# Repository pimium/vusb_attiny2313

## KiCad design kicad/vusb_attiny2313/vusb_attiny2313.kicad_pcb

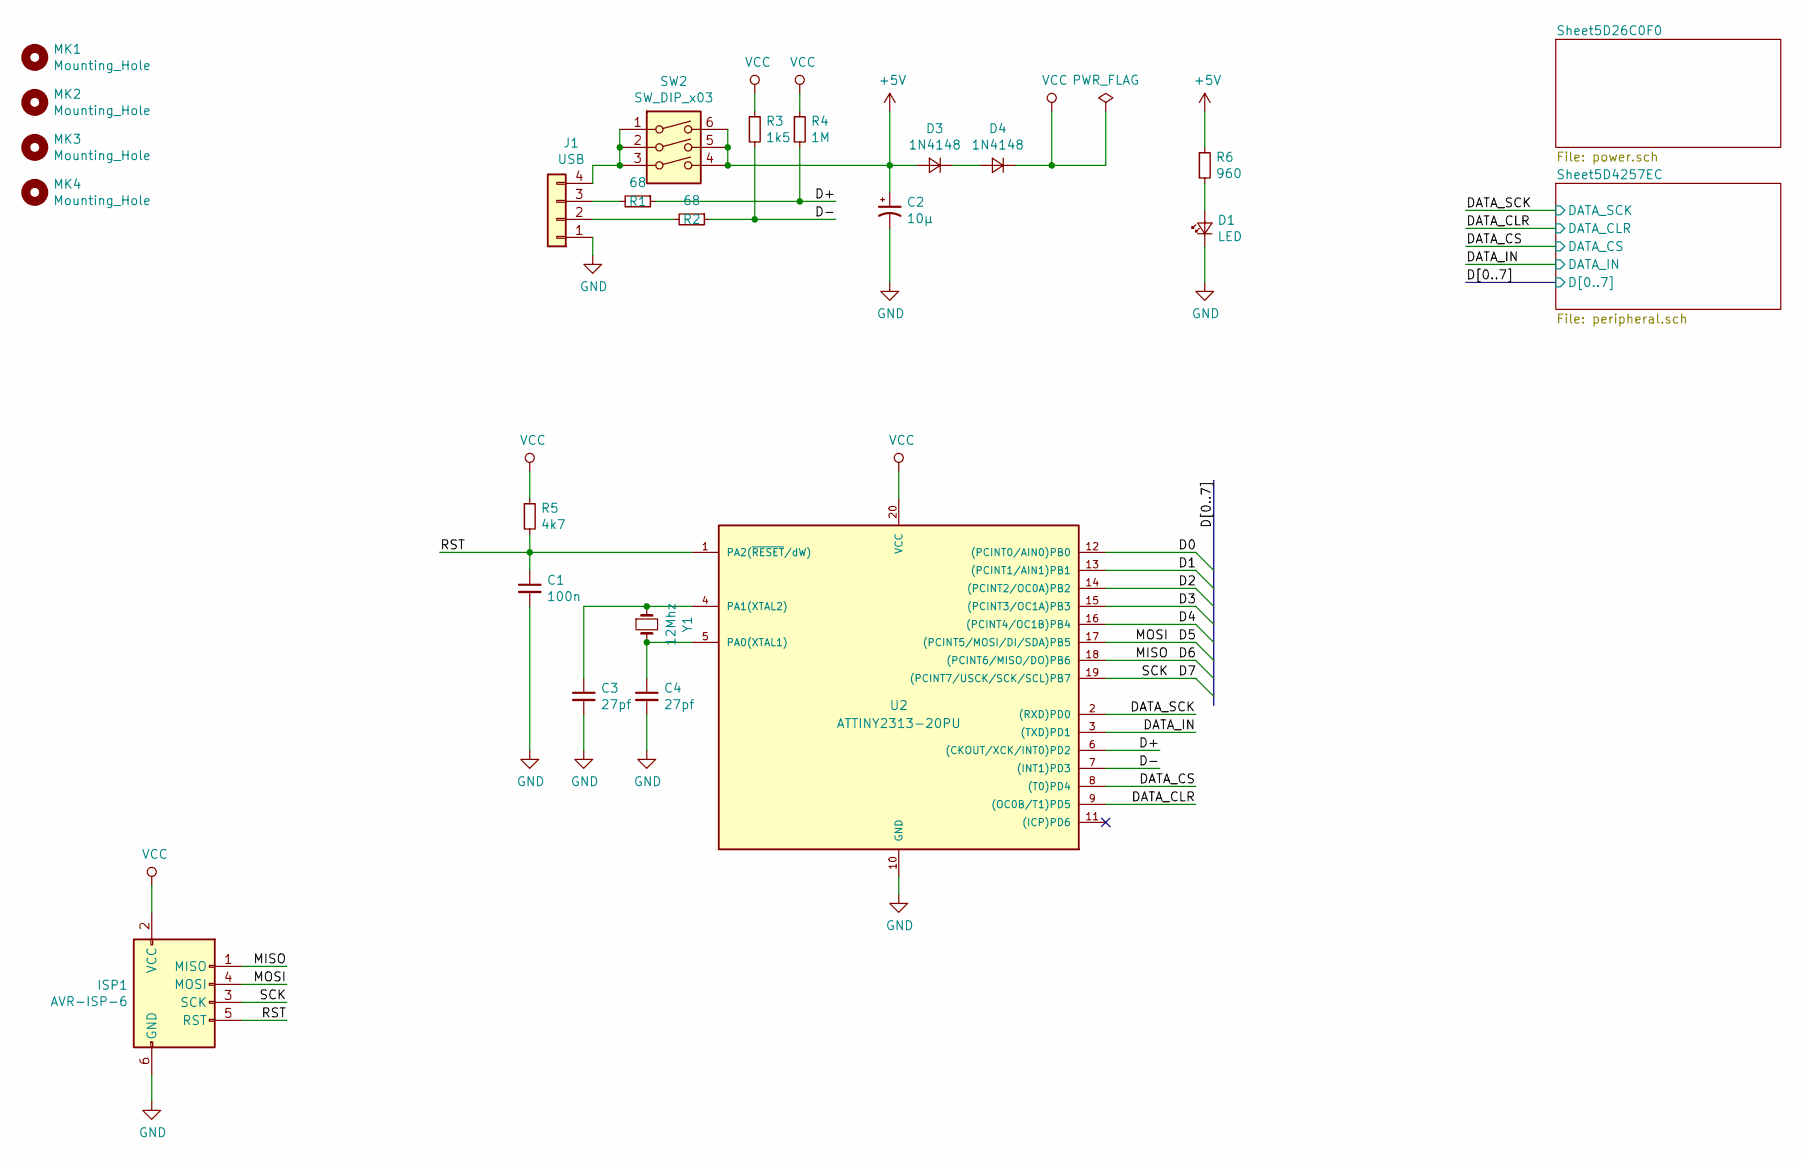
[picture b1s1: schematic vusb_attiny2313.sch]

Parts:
C1: 100n; C_0805_2012Metric_Pad1.15x1.40mm_HandSolder
C2: 10µ; CP_Radial_D5.0mm_P2.50mm
C3, C4: 27pf; C_0805_2012Metric_Pad1.15x1.40mm_HandSolder
D1: LED; LED_1206_3216Metric_Pad1.42x1.75mm_HandSolder
D3, D4: 1N4148; D_MiniMELF_Handsoldering
ISP1: AVR-ISP-6; PinHeader_2x03_P2.54mm_Vertical
J1: USB; PinHeader_1x04_P2.54mm_Vertical
MK1, MK2, MK3, MK4: Mounting_Hole; MountingHole_3.2mm_M3
R1, R2: 68; R_0805_2012Metric_Pad1.15x1.40mm_HandSolder
R3: 1k5; R_0805_2012Metric_Pad1.15x1.40mm_HandSolder
R4: 1M; R_0805_2012Metric_Pad1.15x1.40mm_HandSolder
R5: 4k7; R_0805_2012Metric_Pad1.15x1.40mm_HandSolder
R6: 960; R_0805_2012Metric_Pad1.15x1.40mm_HandSolder
SW2: SW_DIP_x03; DPDT_WIDE_54_54
U2: ATTINY2313-20PU; DIP-20_W7.62mm_LongPads
Y1: 12Mhz; Crystal_HC49-U_Vertical

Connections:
+5V: C2.1, D3.2 (A), R6.1, SW2.4, SW2.5, SW2.6; also elsewhere on the board
/D0: U2.12 ((PCINT0/AIN0)PB0); also elsewhere on the board
/D1: U2.13 ((PCINT1/AIN1)PB1); also elsewhere on the board
/D2: U2.14 ((PCINT2/OC0A)PB2); also elsewhere on the board
/D3: U2.15 ((PCINT3/OC1A)PB3); also elsewhere on the board
/D4: U2.16 ((PCINT4/OC1B)PB4); also elsewhere on the board
/D5: ISP1.4 (MOSI), U2.17 ((PCINT5/MOSI/DI/SDA)PB5); also elsewhere on the board
/D6: ISP1.1 (MISO), U2.18 ((PCINT6/MISO/DO)PB6); also elsewhere on the board
/D7: ISP1.3 (SCK), U2.19 ((PCINT7/USCK/SCK/SCL)PB7); also elsewhere on the board
/D+: R1.1, R4.2, U2.6 ((CKOUT/XCK/INT0)PD2)
/D-: R2.1, R3.2, U2.7 ((INT1)PD3)
/DATA_CLR: U2.9 ((OC0B/T1)PD5); also elsewhere on the board
/DATA_CS: U2.8 ((T0)PD4); also elsewhere on the board
/DATA_IN: U2.3 ((TXD)PD1); also elsewhere on the board
/DATA_SCK: U2.2 ((RXD)PD0); also elsewhere on the board
/RST: C1.1, ISP1.5 (RST), R5.2, U2.1 (PA2(~RESET~/dW))
GND: C1.2, C2.2, C3.2, C4.2, D1.1 (K), ISP1.6 (GND), J1.1, U2.10 (GND); also elsewhere on the board
unnamed: C3.1, U2.4 (PA1(XTAL2)), Y1.1
unnamed: C4.1, U2.5 (PA0(XTAL1)), Y1.2
unnamed: D1.2 (A), R6.2
unnamed: D3.1 (K), D4.2 (A)
unnamed: J1.2, R2.2
unnamed: J1.3, R1.2
unnamed: J1.4, SW2.1, SW2.2, SW2.3
VCC: D4.1 (K), ISP1.2 (VCC), R3.1, R4.1, R5.1, U2.20 (VCC); also elsewhere on the board

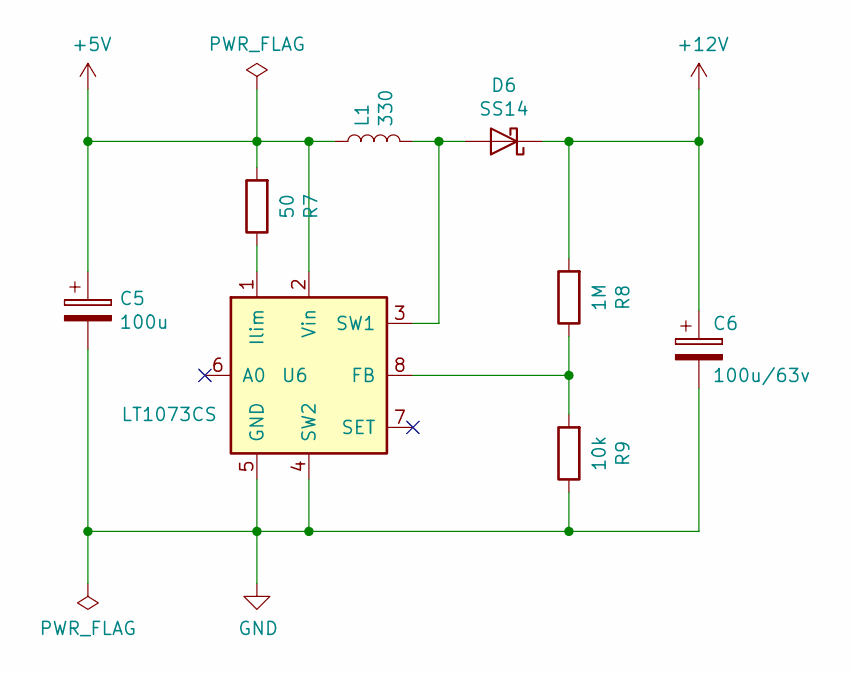
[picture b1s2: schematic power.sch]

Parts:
C5: 100u; CP_EIA-7343-15_Kemet-W_Pad2.25x2.55mm_HandSolder
C6: 100u/63v; CP_Radial_D8.0mm_P5.00mm
D6: SS14; D_SMA_Handsoldering
L1: 330; Choke_CD75
R7: 50; R_0805_2012Metric_Pad1.15x1.40mm_HandSolder
R8: 1M; R_0805_2012Metric_Pad1.15x1.40mm_HandSolder
R9: 10k; R_0805_2012Metric_Pad1.15x1.40mm_HandSolder
U6: LT1073CS; SOIC-8_3.9x4.9mm_P1.27mm

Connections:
+5V: C5.1, L1.1, R7.2, U6.2 (Vin); also elsewhere on the board
+12V: C6.1, D6.1 (K), R8.2; also elsewhere on the board
GND: C5.2, C6.2, R9.1, U6.4 (SW2), U6.5 (GND); also elsewhere on the board
unnamed: D6.2 (A), L1.2, U6.3 (SW1)
unnamed: R7.1, U6.1 (Ilim)
unnamed: R8.1, R9.2, U6.8 (FB)

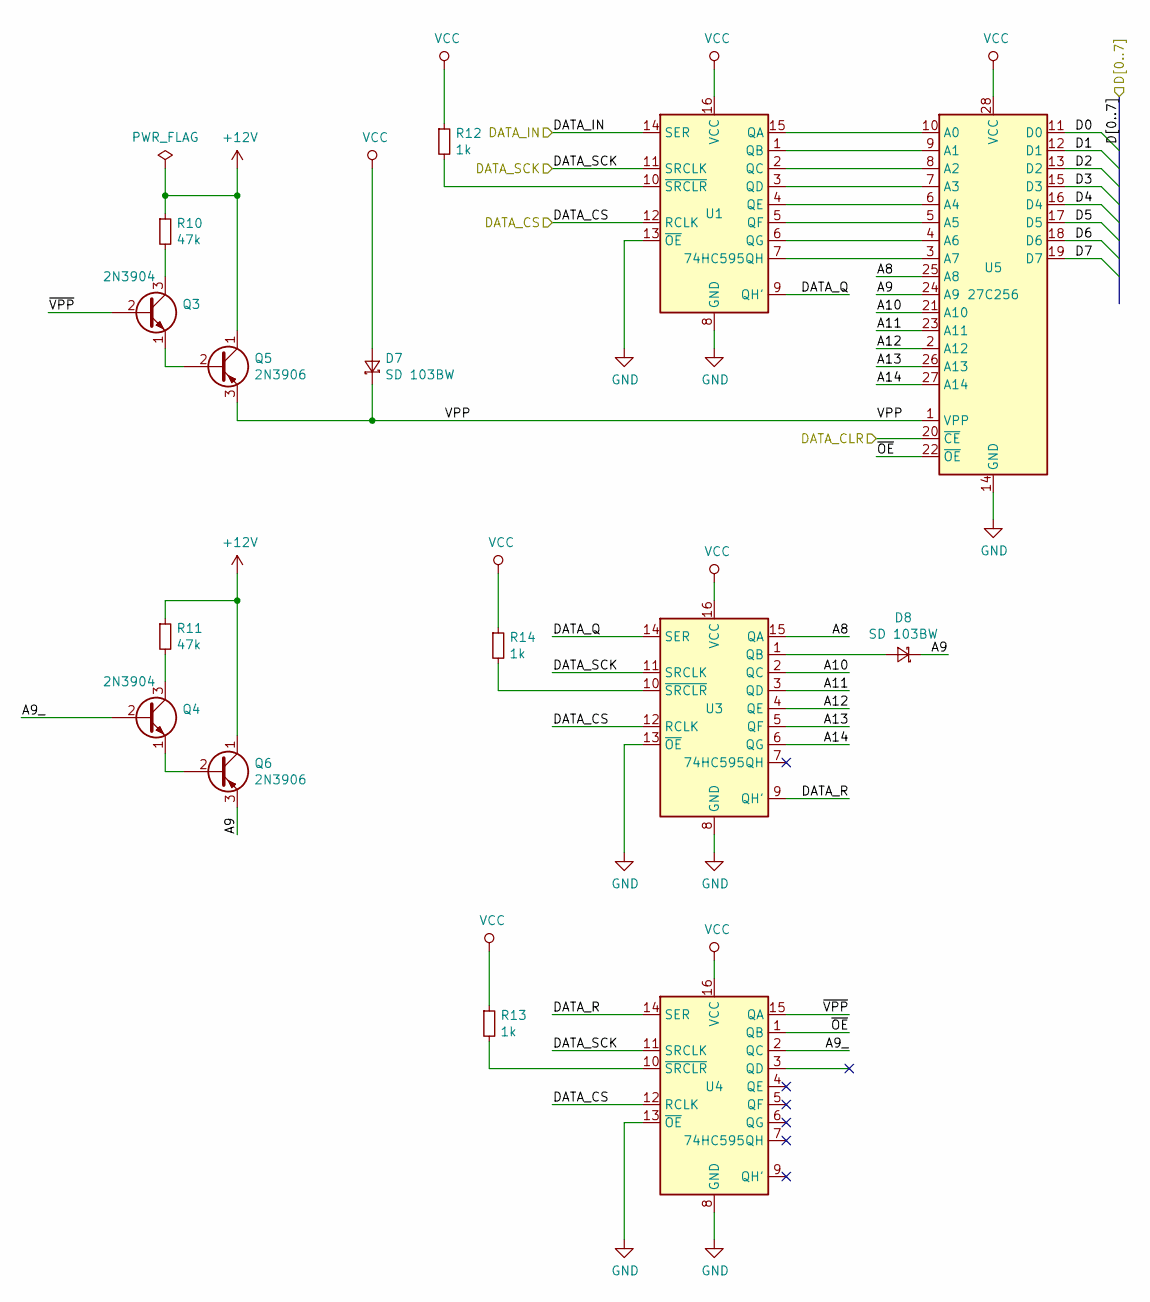
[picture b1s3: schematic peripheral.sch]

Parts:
D7, D8: SD 103BW; D_SOD-123
Q3, Q4: 2N3904; TO-92_Inline_Wide
Q5, Q6: 2N3906; TO-92_Inline_Wide
R10, R11: 47k; R_0805_2012Metric_Pad1.15x1.40mm_HandSolder
R12, R13, R14: 1k; R_0805_2012Metric_Pad1.15x1.40mm_HandSolder
U1, U3, U4: 74HC595; DIP-16_W7.62mm_Socket_LongPads
U5: 27C256; DIP_Socket-28pin_in_32_W11.9_W12.7_W15.24_W17.78_W18.5_3M_2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

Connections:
+12V: Q5.1 (C), Q6.1 (C), R10.1, R11.1; also elsewhere on the board
/D0: U5.11 (D0); also elsewhere on the board
/D1: U5.12 (D1); also elsewhere on the board
/D2: U5.13 (D2); also elsewhere on the board
/D3: U5.15 (D3); also elsewhere on the board
/D4: U5.16 (D4); also elsewhere on the board
/D5: U5.17 (D5); also elsewhere on the board
/D6: U5.18 (D6); also elsewhere on the board
/D7: U5.19 (D7); also elsewhere on the board
/DATA_CLR: U5.20 (~CE); also elsewhere on the board
/DATA_CS: U1.12 (RCLK), U3.12 (RCLK), U4.12 (RCLK); also elsewhere on the board
/DATA_IN: U1.14 (SER); also elsewhere on the board
/DATA_SCK: U1.11 (SRCLK), U3.11 (SRCLK), U4.11 (SRCLK); also elsewhere on the board
/Sheet5D4257EC/A8: U3.15 (QA), U5.25 (A8)
/Sheet5D4257EC/A9: D8.1 (K), Q6.3 (E), U5.24 (A9)
/Sheet5D4257EC/A9_: Q4.2 (B), U4.2 (QC)
/Sheet5D4257EC/A10: U3.2 (QC), U5.21 (A10)
/Sheet5D4257EC/A11: U3.3 (QD), U5.23 (A11)
/Sheet5D4257EC/A12: U3.4 (QE), U5.2 (A12)
/Sheet5D4257EC/A13: U3.5 (QF), U5.26 (A13)
/Sheet5D4257EC/A14: U3.6 (QG), U5.27 (A14)
/Sheet5D4257EC/DATA_Q: U1.9 (QH'), U3.14 (SER)
/Sheet5D4257EC/DATA_R: U3.9 (QH'), U4.14 (SER)
/Sheet5D4257EC/VPP: D7.1 (K), Q5.3 (E), U5.1 (VPP)
/Sheet5D4257EC/~OE: U4.1 (QB), U5.22 (~OE)
/Sheet5D4257EC/~VPP: Q3.2 (B), U4.15 (QA)
GND: U1.8 (GND), U1.13 (~OE), U3.8 (GND), U3.13 (~OE), U4.8 (GND), U4.13 (~OE), U5.14 (GND); also elsewhere on the board
unnamed: D8.2 (A), U3.1 (QB)
unnamed: Q3.1 (E), Q5.2 (B)
unnamed: Q3.3 (C), R10.2
unnamed: Q4.1 (E), Q6.2 (B)
unnamed: Q4.3 (C), R11.2
unnamed: R12.2, U1.10 (~SRCLR)
unnamed: R13.2, U4.10 (~SRCLR)
unnamed: R14.2, U3.10 (~SRCLR)
unnamed: U1.1 (QB), U5.9 (A1)
unnamed: U1.2 (QC), U5.8 (A2)
unnamed: U1.3 (QD), U5.7 (A3)
unnamed: U1.4 (QE), U5.6 (A4)
unnamed: U1.5 (QF), U5.5 (A5)
unnamed: U1.6 (QG), U5.4 (A6)
unnamed: U1.7 (QH), U5.3 (A7)
unnamed: U1.15 (QA), U5.10 (A0)
VCC: D7.2 (A), R12.1, R13.1, R14.1, U1.16 (VCC), U3.16 (VCC), U4.16 (VCC), U5.28 (VCC); also elsewhere on the board

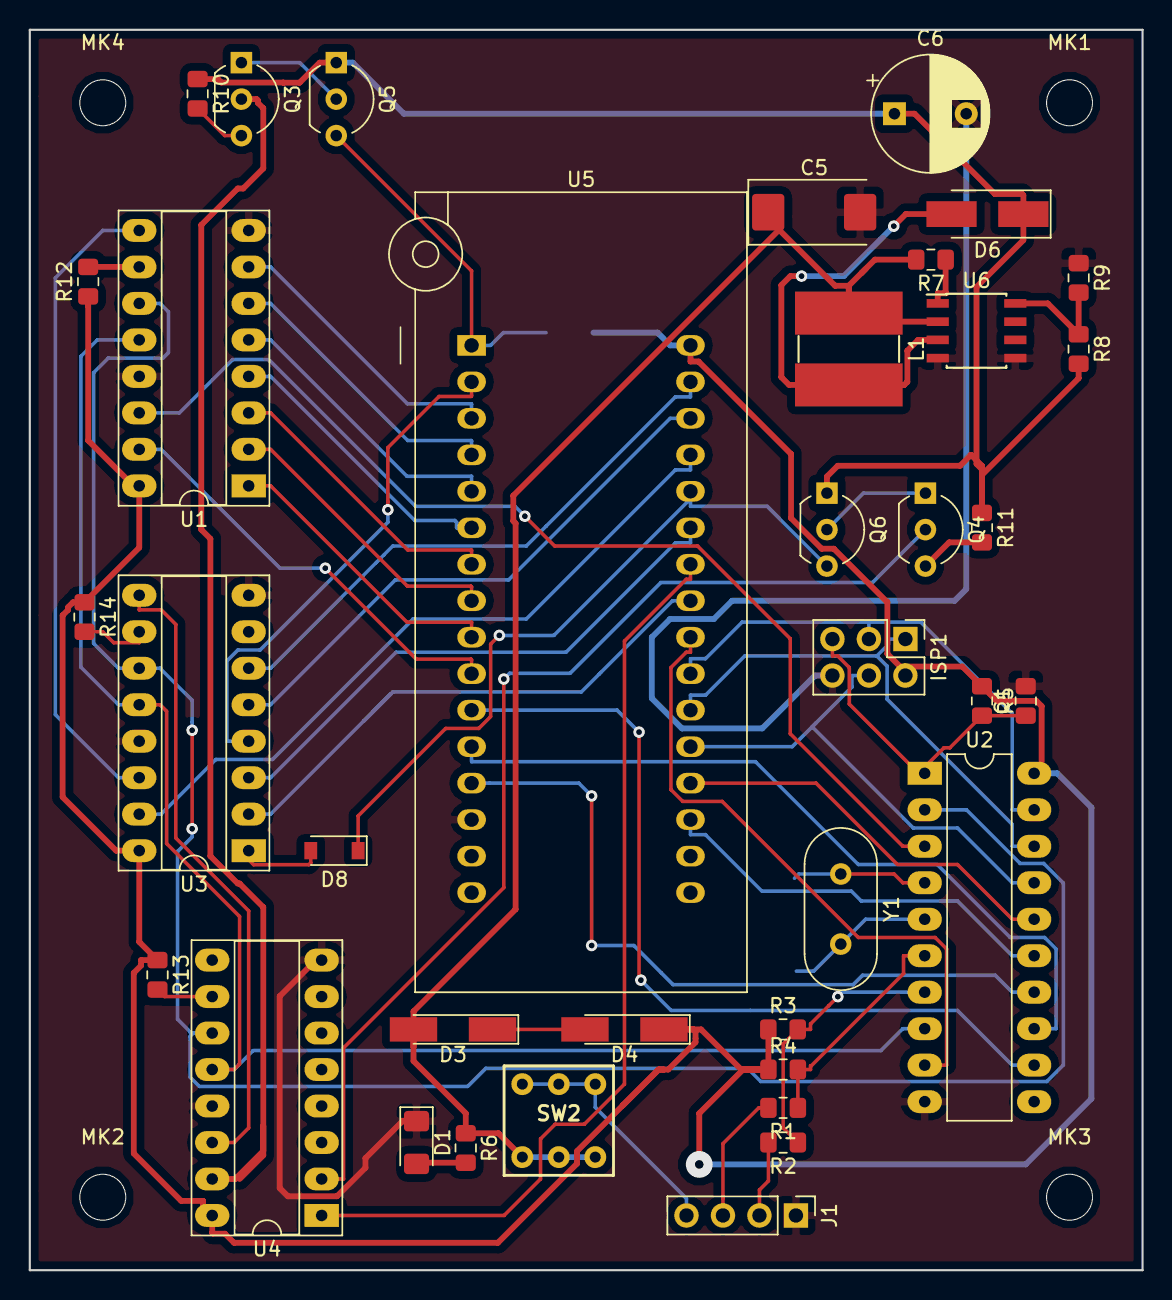
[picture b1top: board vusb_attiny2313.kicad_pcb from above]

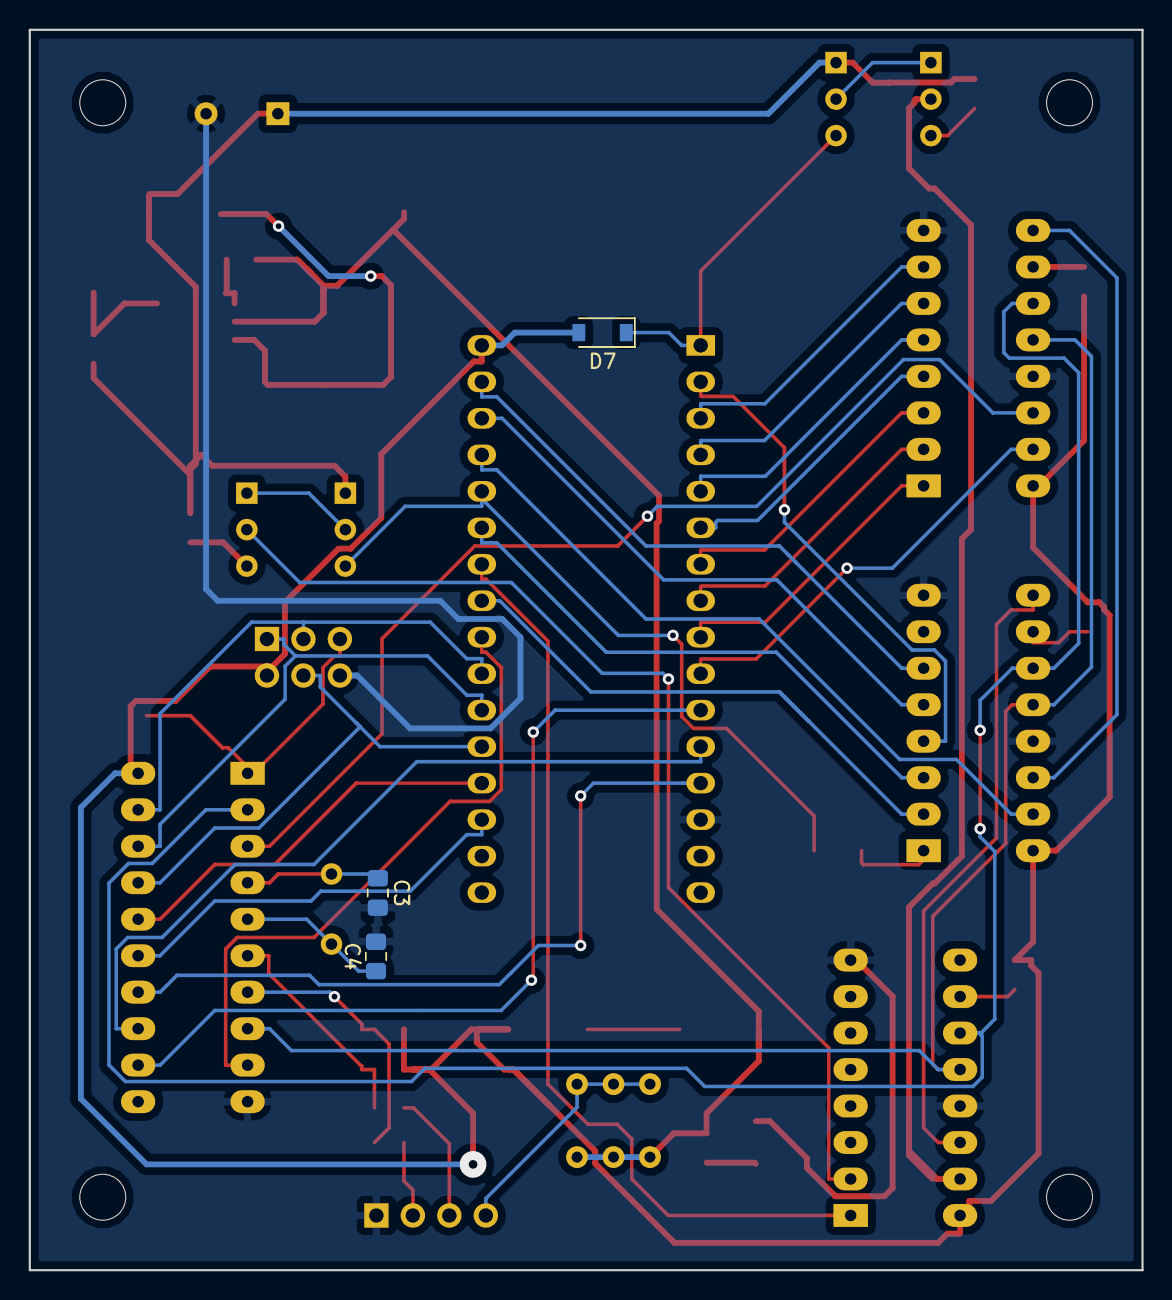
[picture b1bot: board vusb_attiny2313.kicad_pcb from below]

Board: 2 copper layers, 77.5 x 86.4 mm, 44 parts (3 on the bottom side), 58 nets.

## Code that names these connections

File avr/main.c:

/**
 * Project: AVR ATtiny USB Tutorial at http://codeandlife.com/
 * Author: Joonas Pihlajamaa, joonas.pihlajamaa@iki.fi
 * Inspired by V-USB example code by Christian Starkjohann
 * Copyright: (C) 2012 by Joonas Pihlajamaa
 * License: GNU GPL v3 (see License.txt)
 */
#include <avr/interrupt.h>
#include <avr/io.h>
#include <avr/wdt.h>

#include "usbdrv.h"

#ifndef F_CPU
#define F_CPU 12000000L
#endif

#include <util/delay.h>

#define USB_LED 0x30
#define USB_LED_ON 0x31
#define USB_DATA_READ 2
#define USB_DATA_WRITE 3
#define USB_DATA_READ_DEVICE_CODE 4

#define MESSAGE_LENGTH 8
#define RCLK PD4
#define DATA PD1
#define SRCLK PD0

#define RAM_WE 0x80
#define RAM_OE 0x40
#define RAM_A9 0x20
#define RAM_CE PD5

void vfd_write_byte(uint8_t byte);

uchar replyBuf[20] = "Hello,USB!";
int len;
uint8_t address[2];

/* The following variables store the status of the current data transfer */
volatile uchar bytesRemaining;

// this gets called when custom control message is received
USB_PUBLIC uchar usbFunctionSetup(uchar data[8])
{
    usbRequest_t *rq = (void *)data; // cast data to correct type
    uint8_t choice = RAM_A9;

    switch (rq->bRequest)
    { // custom command is in the bRequest field
    case USB_LED_ON:
        PORTD |= (1 << PD5); // turn LED on
        return 0;

    case USB_LED:
        if (rq->wValue.bytes[0])
            PORTD |= (1 << PD5); // turn LED on
        else
            PORTD &= ~(1 << PD5); // turn LED off
        return 0;

    case USB_DATA_READ_DEVICE_CODE: // send data to PC
        choice = 0;
    case USB_DATA_READ: // send data to PC

        PORTD |= (1 << RAM_CE);
        DDRB = 0x00;
        PORTB = 0xFF;

        PORTD &= ~(1 << SRCLK);
        PORTD |= (1 << RCLK);
        PORTD &= ~(1 << RCLK);
        vfd_write_byte(RAM_OE | RAM_WE | choice);
        vfd_write_byte(rq->wValue.bytes[1]);
        vfd_write_byte(rq->wValue.bytes[0]);
        PORTD |= (1 << RCLK);

        PORTD &= ~(1 << SRCLK);
        PORTD |= (1 << RCLK);
        PORTD &= ~(1 << RCLK);
        vfd_write_byte(RAM_WE | choice);
        vfd_write_byte(rq->wValue.bytes[1]);
        vfd_write_byte(rq->wValue.bytes[0]);
        PORTD &= ~(1 << RAM_CE);
        PORTD |= (1 << RCLK);

        PORTD &= ~(1 << SRCLK);
        PORTD |= (1 << RCLK);
        PORTD &= ~(1 << RCLK);

        replyBuf[0] = PINB;

        vfd_write_byte(RAM_OE | RAM_WE | choice);
        vfd_write_byte(rq->wValue.bytes[1]);
        vfd_write_byte(rq->wValue.bytes[0]);
        PORTD |= (1 << RCLK);
        PORTD |= (1 << RAM_CE);
        usbMsgPtr = replyBuf;
        return 1;

    case USB_DATA_WRITE: // receive data from PC
        bytesRemaining = (uchar)rq->wLength.word;
        address[1] = rq->wValue.bytes[1];
        address[0] = rq->wValue.bytes[0];

        return USB_NO_MSG;

    default:
        return 0;
    }

    return 0; // should not get here
}

/* usbFunctionWrite() is called when the host sends a chunk of data to the
 * device. For more information see the documentation in usbdrv/usbdrv.h.
 */
USB_PUBLIC uchar usbFunctionWrite(uchar *data, uchar len)
{
    PORTD |= (1 << RAM_CE);
    DDRB = 0xFF;
    PORTB = data[0];

    PORTD &= ~(1 << SRCLK);
    PORTD |= (1 << RCLK);
    PORTD &= ~(1 << RCLK);
    vfd_write_byte(RAM_OE | RAM_A9);
    vfd_write_byte(address[1]);
    vfd_write_byte(address[0]);
    PORTD |= (1 << RCLK);

    PORTD &= ~(1 << SRCLK);
    PORTD |= (1 << RCLK);
    PORTD &= ~(1 << RCLK);
    vfd_write_byte(RAM_OE | RAM_WE | RAM_A9);
    vfd_write_byte(address[1]);
    vfd_write_byte(address[0]);

    PORTD &= ~(1 << RAM_CE);

    PORTD |= (1 << RCLK);

    PORTD &= ~(1 << SRCLK);
    PORTD |= (1 << RCLK);
    PORTD &= ~(1 << RCLK);
    vfd_write_byte(RAM_OE | RAM_A9);
    vfd_write_byte(address[1]);
    vfd_write_byte(address[0]);
    PORTD |= (1 << RCLK);

    PORTD |= (1 << RAM_CE);

    return 1; /* return 1 if this was the last chunk */
}

void vfd_write_byte(uint8_t byte)
{
    int i = MESSAGE_LENGTH;
    do
    {
        if (byte & 0x01)
            PORTD |= (1 << DATA);
        else
            PORTD &= ~(1 << DATA);

        PORTD &= ~(1 << SRCLK);
        byte = byte >> 1;
        i--;

        PORTD |= (1 << SRCLK);
    } while (i > 0);
    PORTD &= ~(1 << SRCLK);
    wdt_reset();
}

int main()
{
    uchar i;

    DDRD |= (1 << PD4) | (1 << PD5) | (1 << PD0) | (1 << PD1);
    PORTD |= (1 << PD4) | (1 << PD5) | (1 << PD0) | (1 << PD1);

    wdt_enable(WDTO_1S); // enable 1s watchdog timer

    usbInit();

    usbDeviceDisconnect(); // enforce re-enumeration
    for (i = 0; i < 250; i++)
    {                // wait 500 ms
        wdt_reset(); // keep the watchdog happy
        _delay_ms(2);
    }
    usbDeviceConnect();

    sei();               // Enable interrupts after re-enumeration
    PORTD |= (1 << PD5); // turn LED on

    while (1)
    {
        wdt_reset(); // keep the watchdog happy
        usbPoll();
    }
    return 0;
}

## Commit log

2017-12-22 compilation succes
2017-12-27 kicad board done
2017-12-30 work fine have to be refine
2018-01-03 first revision, kernel and avr part work. Kernel code have to be refine
2018-01-03 forget files
2018-01-04 forgotten files
2018-01-30 gitignore
2018-02-04 Clion cmake done !!!
2018-02-22 gitignore for kicad
2018-02-25 rm build dir from git
2018-02-25 clion
2018-02-26 Add label to the board
2019-07-07 Updated!!
2019-07-10 add 27c256
2019-07-12 schematic done
2019-07-12 kernel and user space update
2019-07-24 right timing now, reading and writing from adresse 0
2019-08-24 fuses angepasst!
2019-08-24 Pin zu neuen board angepasst!
2019-08-25 fertig for pcb
